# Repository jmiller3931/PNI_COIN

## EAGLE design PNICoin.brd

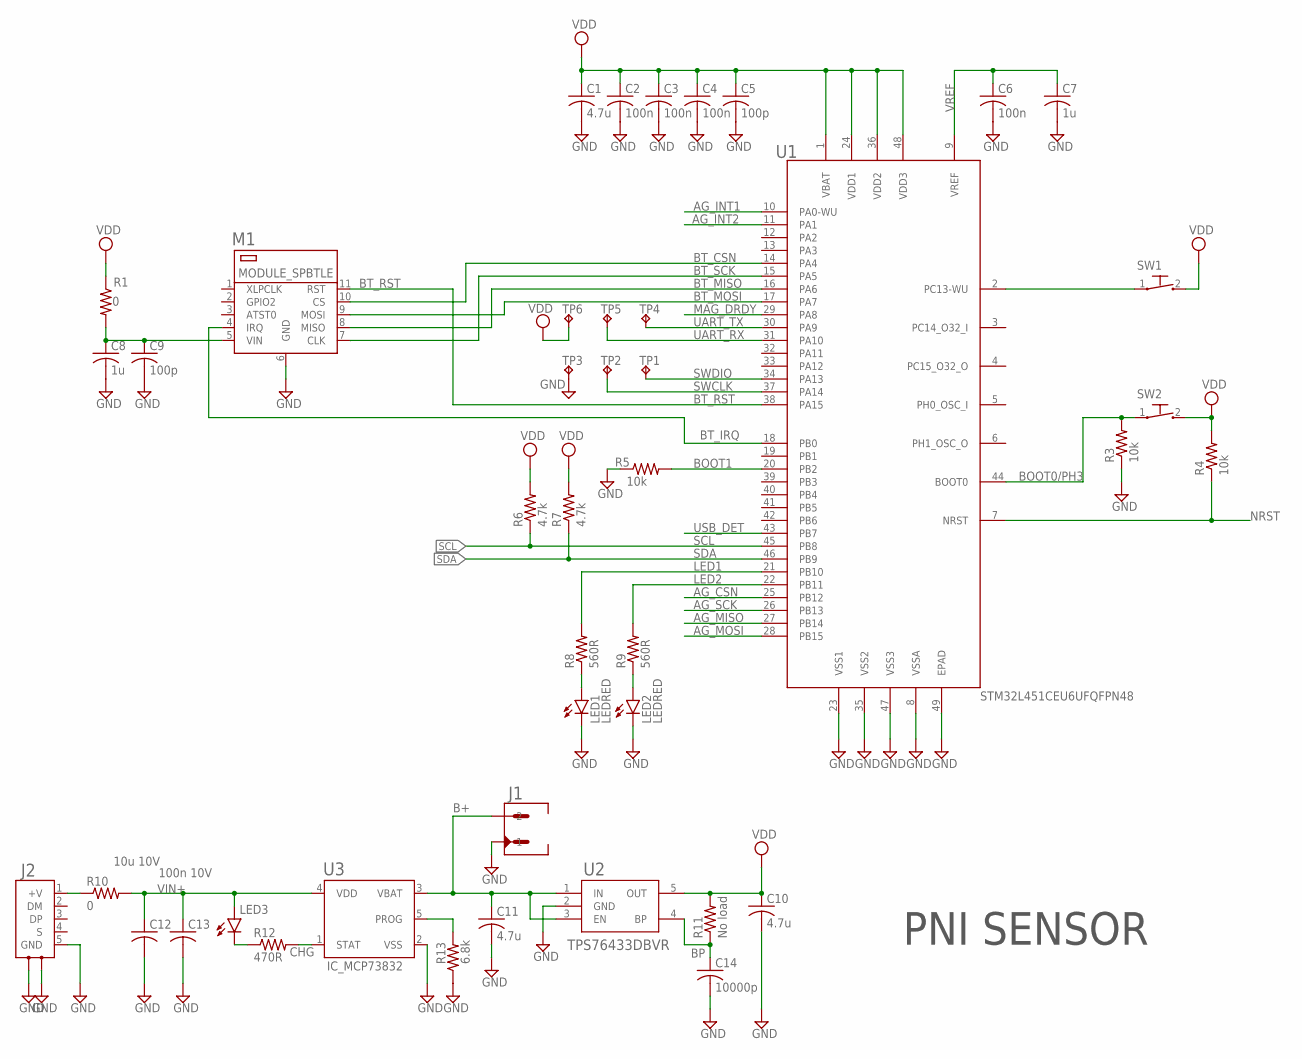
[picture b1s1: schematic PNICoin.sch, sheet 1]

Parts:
C1, C10, C11: 4.7u; C0402K
C2, C3, C4, C6: 100n; C0402K
C5, C9: 100p; C0402K
C7, C8: 1u; C0402K
C12: 10u 10V; C0402K
C13: 100n 10V; C0402K
C14: 10000p; C0402K
J1: CONN_HDR_PICO_EZMATE_2P; CON_HDR_PICO-EZMATE_2P
J2: CONN_MICROUSB_HIROSE_XZ024_SMD; CON_MICROUSB_HIROSE_XZ024_SMD
LED1, LED2, LED3: LEDRED; LED_0402
M1: MODULE_SPBTLE
R1, R10: 0; R0402
R3, R4, R5: 10k; R0402
R6, R7: 4.7k; R0402
R8, R9: 560R; R0402
R11: No load; R0402
R12: 470R; R0402
R13: 6.8k; R0402
SW1, SW2: SW_PB; SW-PB_B3U-3000PB
TP1, TP2, TP3, TP4, TP5, TP6: TPTP06R; TP06R
U1: STM32L451CEU6UFQFPN48; QFN50P700X700X60-49T560
U2: TPS76433DBVR; DBV5
U3: IC_MCP73832; SOT95P240X125-5

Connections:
AG_CSN: U1.25 (PB12); also elsewhere on the board
AG_INT1: U1.10 (PA0-WU); also elsewhere on the board
AG_INT2: U1.11 (PA1); also elsewhere on the board
AG_MISO: U1.27 (PB14); also elsewhere on the board
AG_MOSI: U1.28 (PB15); also elsewhere on the board
AG_SCK: U1.26 (PB13); also elsewhere on the board
B+: C11.1, J1.2, U2.1 (IN), U2.3 (EN), U3.3 (VBAT)
BLEV+: C8.1, C9.1, M1.5 (VIN), R1.2
BOOT0/PH3: R3.2, SW2.1, U1.44 (BOOT0)
BOOT1: R5.2, U1.20 (PB2)
BP: C14.1, R11.1, U2.4 (BP)
BT_CSN: M1.10 (CS), U1.14 (PA4)
BT_IRQ: M1.4 (IRQ), U1.18 (PB0)
BT_MISO: M1.8 (MISO), U1.16 (PA6)
BT_MOSI: M1.9 (MOSI), U1.17 (PA7)
BT_RST: M1.11 (RST), U1.38 (PA15)
BT_SCK: M1.7 (CLK), U1.15 (PA5)
CHG: R12.2, U3.1 (STAT)
GND: C1.2, C2.2, C3.2, C4.2, C5.2, C6.2, C7.2, C8.2, C9.2, C10.2, C11.2, C12.2, C13.2, C14.2, J1.1, J2.5 (GND), J2.6 (SH1), J2.7 (SH2), LED1.K (C), LED2.K (C), M1.6 (GND), R3.1, R5.1, R13.1, TP3.TP, U1.8 (VSSA), U1.23 (VSS1), U1.35 (VSS2), U1.47 (VSS3), U1.49 (EPAD), U2.2 (GND), U3.2 (VSS); also elsewhere on the board
LED1: R8.2, U1.21 (PB10)
LED1A: LED1.A, R8.1
LED2: R9.2, U1.22 (PB11)
LED2A: LED2.A, R9.1
LED3K: LED3.K (C), R12.1
MAG_DRDY: U1.29 (PA8); also elsewhere on the board
NRST: R4.1, U1.7 (NRST)
PROG: R13.2, U3.5 (PROG)
SCL: R6.1, U1.45 (PB8); also elsewhere on the board
SDA: R7.1, U1.46 (PB9); also elsewhere on the board
SW1: SW1.1, U1.2 (PC13-WU)
SWCLK: TP2.TP, U1.37 (PA14)
SWDIO: TP1.TP, U1.34 (PA13)
UART_RX: TP5.TP, U1.31 (PA10)
UART_TX: TP4.TP, U1.30 (PA9)
USB_DET: U1.43 (PB7)
VDD: C1.1, C2.1, C3.1, C4.1, C5.1, C10.1, R1.1, R4.2, R6.2, R7.2, R11.2, SW1.2, SW2.2, TP6.TP, U1.1 (VBAT), U1.24 (VDD1), U1.36 (VDD2), U1.48 (VDD3), U2.5 (OUT); also elsewhere on the board
VIN: J2.1 (+V), R10.1
VIN+: C12.1, C13.1, LED3.A, R10.2, U3.4 (VDD)
VREF: C6.1, C7.1, U1.9 (VREF)

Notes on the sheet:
PNI SENSOR

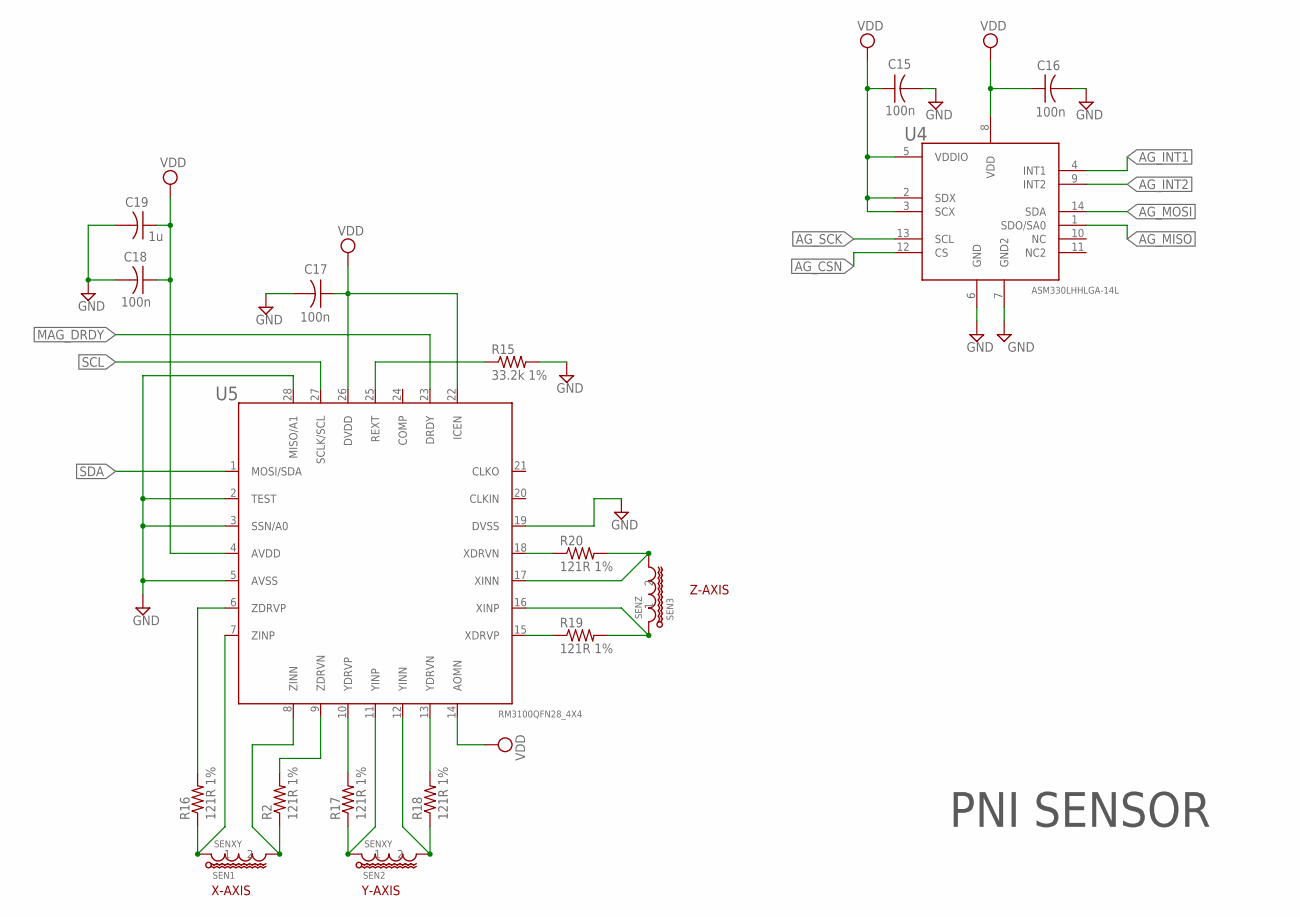
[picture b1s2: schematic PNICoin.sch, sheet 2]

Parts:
C15, C16, C17, C18: 100n; C0402K
C19: 1u; C0402K
R2, R16, R17, R18, R19, R20: 121R 1%; R0402
R15: 33.2k 1%; R0402
SEN1, SEN2: SENXY
SEN3: SENZ
U4: ASM330LHHLGA-14L; QFN50P300X250X86-14
U5: RM3100QFN28_4X4; QFN40P400X400X80-29T250

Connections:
AG_CSN: U4.12 (CS); also elsewhere on the board
AG_INT1: U4.4 (INT1); also elsewhere on the board
AG_INT2: U4.9 (INT2); also elsewhere on the board
AG_MISO: U4.1 (SDO/SA0); also elsewhere on the board
AG_MOSI: U4.14 (SDA); also elsewhere on the board
AG_SCK: U4.13 (SCL); also elsewhere on the board
GND: C15.2, C16.2, C17.2, C18.2, C19.2, R15.2, U4.6 (GND), U4.7 (GND2), U5.2 (TEST), U5.3 (SSN/A0), U5.5 (AVSS), U5.19 (DVSS), U5.28 (MISO/A1); also elsewhere on the board
MAG_DRDY: U5.23 (DRDY); also elsewhere on the board
REXT: R15.1, U5.25 (REXT)
SCL: U5.27 (SCLK/SCL); also elsewhere on the board
SDA: U5.1 (MOSI/SDA); also elsewhere on the board
VDD: C15.1, C16.1, C17.1, C18.1, C19.1, U4.2 (SDX), U4.3 (SCX), U4.5 (VDDIO), U4.8 (VDD), U5.4 (AVDD), U5.14 (AOMN), U5.22 (ICEN), U5.26 (DVDD); also elsewhere on the board
XDN: R20.1, U5.18 (XDRVN)
XDP: R19.1, U5.15 (XDRVP)
XIN: R20.2, SEN3.2, U5.17 (XINN)
XIP: R19.2, SEN3.1, U5.16 (XINP)
YDN: R18.2, U5.13 (YDRVN)
YDP: R17.2, U5.10 (YDRVP)
YIN: R18.1, SEN2.2, U5.12 (YINN)
YIP: R17.1, SEN2.1, U5.11 (YINP)
ZDN: R2.2, U5.9 (ZDRVN)
ZDP: R16.2, U5.6 (ZDRVP)
ZIN: R2.1, SEN1.2, U5.8 (ZINN)
ZIP: R16.1, SEN1.1, U5.7 (ZINP)

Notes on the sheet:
PNI SENSOR
X-AXIS
Y-AXIS
Z-AXIS

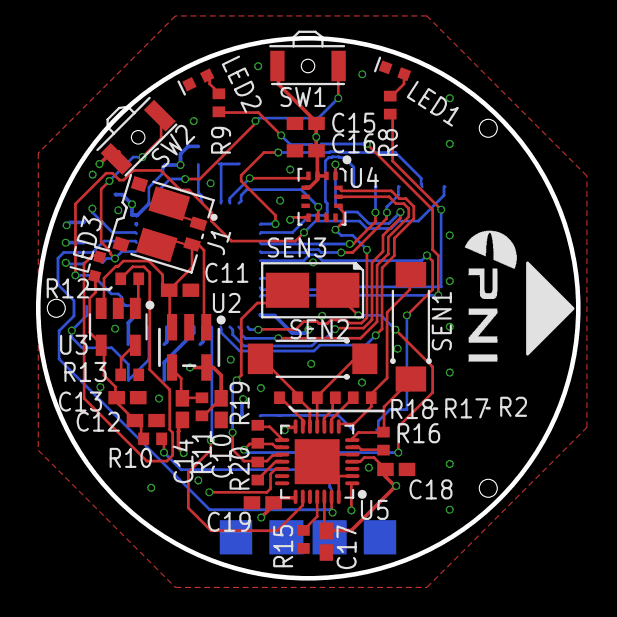
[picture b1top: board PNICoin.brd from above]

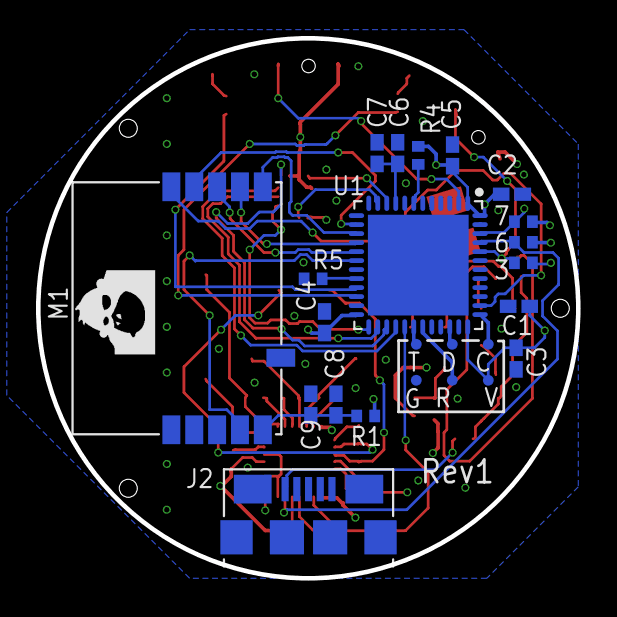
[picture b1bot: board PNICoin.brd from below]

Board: 4 copper layers, 30.0 x 30.0 mm, 62 parts (24 on the bottom side), 51 nets.

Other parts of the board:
DOC1: DOCFIELD
DOC2: LETTER_L

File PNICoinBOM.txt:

Partlist exported from C:/Users/jmiller/Documents/EAGLE/projects/PNI_COIN/PNICoin.sch at 2/7/2019 10:05 AM

Qty Value                          Device                         Package                       Parts                                   Description                MN                MP                SPICEPREFIX TP_SIGNAL_NAME
2   0                              R-US_R0402                     R0402                         R1, R10                                 RESISTOR, American symbol                                      R                         
1   10000p                         C-USC0402K                     C0402K                        C14                                     CAPACITOR, American symbol                                     C                         
9   100n                           C-USC0402K                     C0402K                        C2, C3, C4, C6, C13, C15, C16, C17, C18 CAPACITOR, American symbol                                     C                         
2   100p                           C-USC0402K                     C0402K                        C5, C9                                  CAPACITOR, American symbol                                     C                         
3   10k                            R-US_R0402                     R0402                         R3, R4, R5                              RESISTOR, American symbol                                      R                         
1   10u                            C-USC0402K                     C0402K                        C12                                     CAPACITOR, American symbol                                     C                         
6   120R 1%                        R-US_R0402                     R0402                         R2, R16, R17, R18, R19, R20             RESISTOR, American symbol                                      R                         
3   1u                             C-USC0402K                     C0402K                        C7, C8, C19                             CAPACITOR, American symbol                                     C                         
1   33.2k 1%                       R-US_R0402                     R0402                         R15                                     RESISTOR, American symbol                                      R                         
1   4.7U                           C-USC0402K                     C0402K                        C11                                     CAPACITOR, American symbol                                     C                         
1   4.7k                           C-USC0402K                     C0402K                        C10                                     CAPACITOR, American symbol                                     C                         
2   4.7k                           R-US_R0402                     R0402                         R6, R7                                  RESISTOR, American symbol                                      R                         
1   4.7u                           C-USC0402K                     C0402K                        C1                                      CAPACITOR, American symbol                                     C                         
1   470                            R-US_R0402                     R0402                         R12                                     RESISTOR, American symbol                                      R                         
2   560R                           R-US_R0402                     R0402                         R8, R9                                  RESISTOR, American symbol                                      R                         
1   6.8k                           R-US_R0402                     R0402                         R13                                     RESISTOR, American symbol                                      R                         
1   ASM330LHHLGA-14L               ASM330LHHLGA-14L               QFN50P300X250X86-14           U4                                                                 ST                ASM330LHH                                   
1   CONN_HDR_PICO_EZMATE_2P        CONN_HDR_PICO_EZMATE_2P        CON_HDR_PICO-EZMATE_2P        J1                                                                 Molex             0781710002                                  
1   CONN_MICROUSB_HIROSE_XZ024_SMD CONN_MICROUSB_HIROSE_XZ024_SMD CON_MICROUSB_HIROSE_XZ024_SMD J2                                                                 Hirose            ZX62-AB-5PA(31)                             
1   IC_MCP73832                    IC_MCP73832                    SOT95P240X125-5               U3                                                                 Microchip         MCP73832T-2ACI/OT                           
3   LEDRED                         LEDRED                         LED_0402                      LED1, LED2, LED3                        LED generic 0402           QT Brightek       QBLP595-R                                   
1   MODULE_SPBTLE                  MODULE_SPBTLE                  MODULE_SPBTLE                 M1                                                                 ST                SPBTLE-RFTR                                 
1   No load                        R-US_R0402                     R0402                         R11                                     RESISTOR, American symbol                                      R                         
1   RM3100QFN28_4X4                RM3100QFN28_4X4                QFN40P400X400X80-29T250       U5                                                                 PNI Sensor        13156                                       
2   SENXY                          SENXY                          SENXY                         SEN1, SEN2                                                         PNI Sensor        13104                                       
1   SENZ                           SENZ                           SENZ                          SEN3                                                               PNI Sensor        13101                                       
1   STM32L451CEU6UFQFPN48          STM32L451CEU6UFQFPN48          QFN50P700X700X60-49T560       U1                                                                 ST                STM32L451CEU6                               
2   SW_PB                          SW_PB                          SW-PB_B3U-3000PB              SW1, SW2                                                           Omron Electronics B3U-3000P-B                                 
1   TPS76433DBVR                   TPS76433DBVR                   DBV5                          U2                                                                 TI                TPS76433DBVR                                
6   TPTP06R                        TPTP06R                        TP06R                         TP1, TP2, TP3, TP4, TP5, TP6            Test pad

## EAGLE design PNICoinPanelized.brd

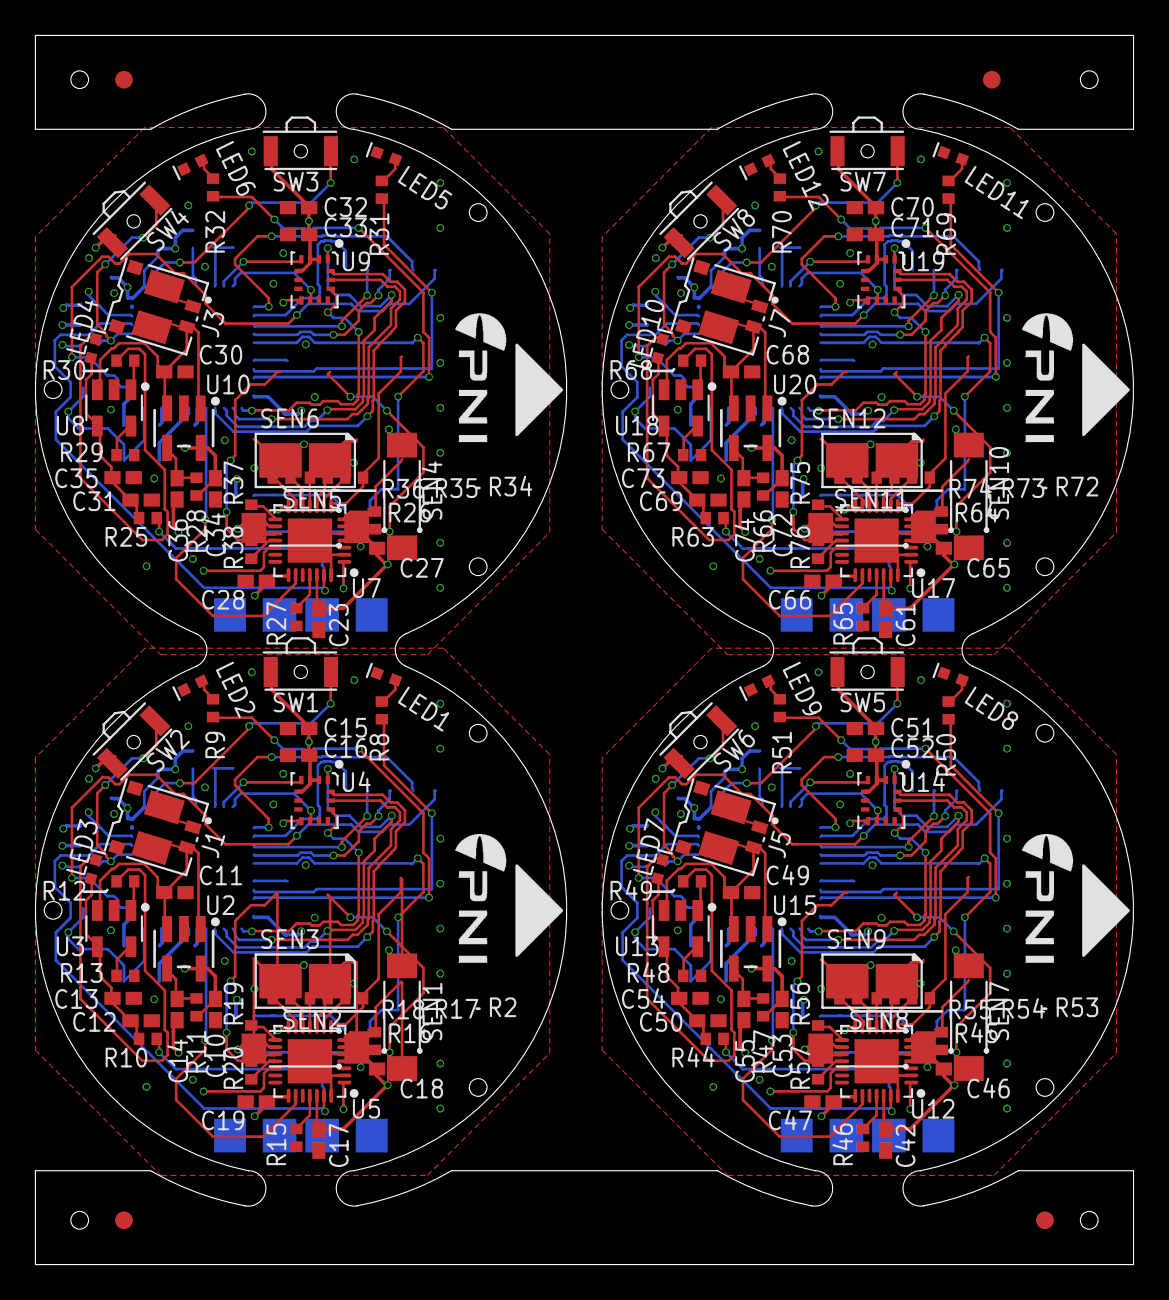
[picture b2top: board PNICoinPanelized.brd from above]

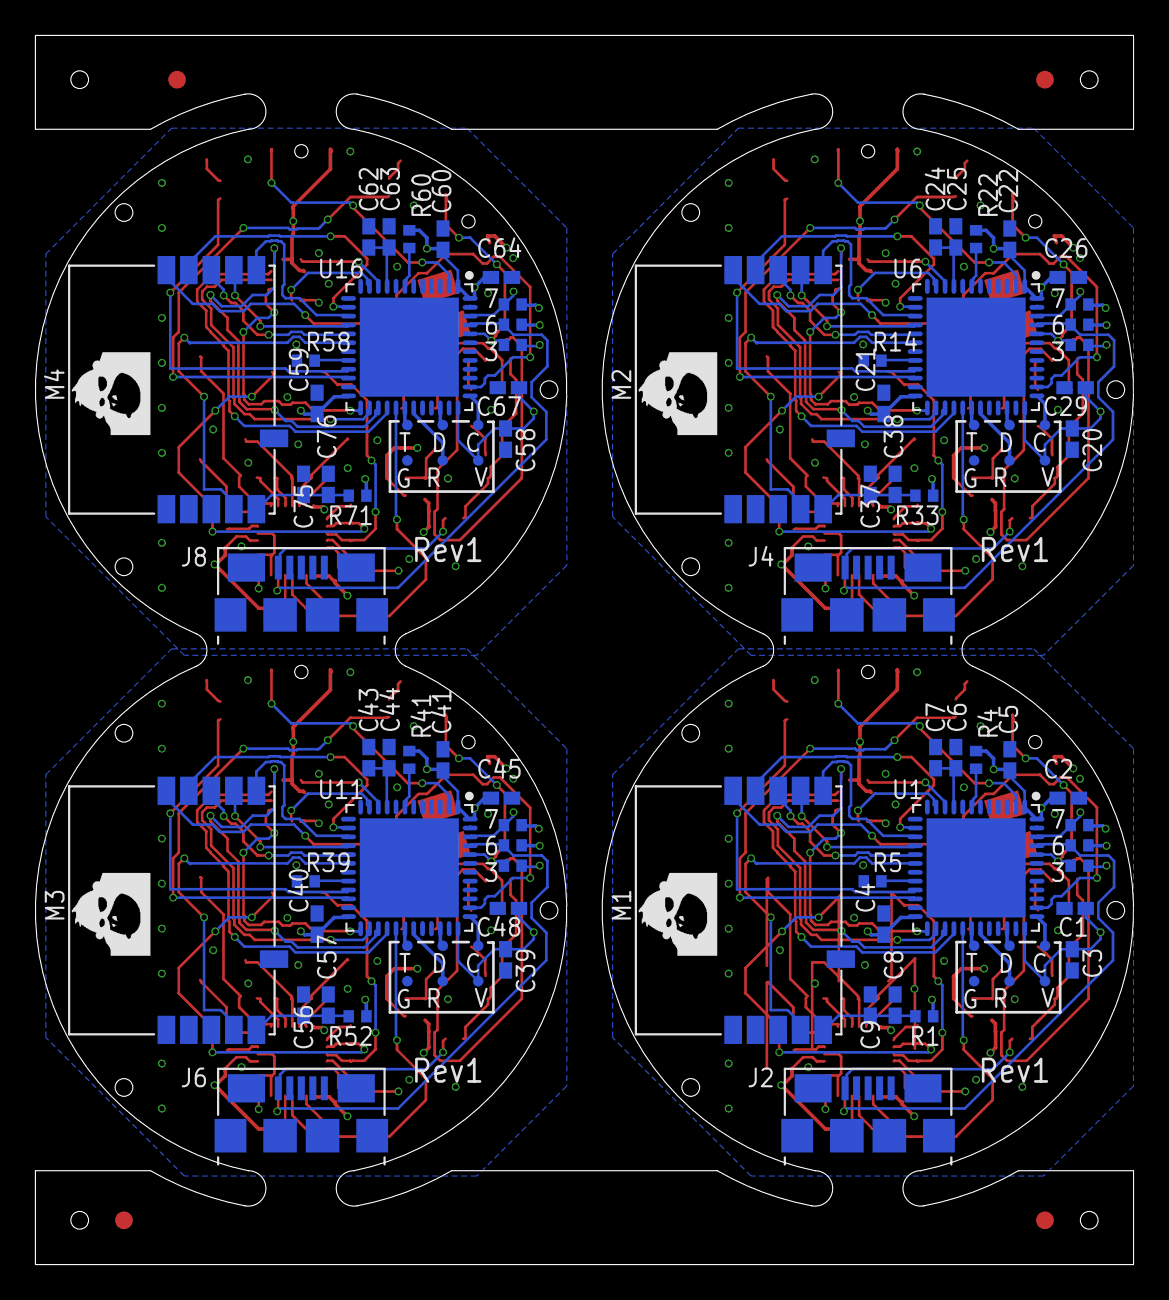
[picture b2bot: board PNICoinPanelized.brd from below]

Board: 4 copper layers, 62.0 x 69.4 mm, 242 parts (96 on the bottom side), 204 nets.

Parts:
C1, C29, C48, C67: 4.7u; C0402K
C2, C3, C4, C6, C13, C15, C16, C17, C18, C20, C21, C23, C25, C26, C27, C32, C33, C35, C39, C40, C42, C44, C45, C46, C51, C52, C54, C58, C59, C61, C63, C64, C65, C70, C71, C73: 100n; C0402K
C5, C9, C22, C37, C41, C56, C60, C75: 100p; C0402K
C7, C8, C19, C24, C28, C38, C43, C47, C57, C62, C66, C76: 1u; C0402K
C10, C34, C53, C72: 4.7k; C0402K
C11, C30, C49, C68: 4.7U; C0402K
C12, C31, C50, C69: 10u; C0402K
C14, C36, C55, C74: 10000p; C0402K
DOC1: DOCFIELD
DOC2: LETTER_L
J1, J3, J5, J7: CONN_HDR_PICO_EZMATE_2P; CON_HDR_PICO-EZMATE_2P
J2, J4, J6, J8: CONN_MICROUSB_HIROSE_XZ024_SMD; CON_MICROUSB_HIROSE_XZ024_SMD
LED1, LED2, LED3, LED4, LED5, LED6, LED7, LED8, LED9, LED10, LED11, LED12: LED; LED_0402
M1, M2, M3, M4: MODULE_SPBTLE
R1, R10, R25, R33, R44, R52, R63, R71: 0; R0402
R2, R16, R17, R18, R19, R20, R26, R34, R35, R36, R37, R38, R45, R53, R54, R55, R56, R57, R64, R72, R73, R74, R75, R76: 120R 1%; R0402
R3, R4, R5, R14, R21, R22, R39, R40, R41, R58, R59, R60: 10k; R0402
R6, R7, R23, R24, R42, R43, R61, R62: 4.7k; R0402
R8, R9, R31, R32, R50, R51, R69, R70: 560R; R0402
R11, R28, R47, R66: No load; R0402
R12, R30, R49, R68: 470; R0402
R13, R29, R48, R67: 6.8k; R0402
R15, R27, R46, R65: 33.2k 1%; R0402
SEN1, SEN2, SEN4, SEN5, SEN7, SEN8, SEN10, SEN11: SENXY
SEN3, SEN6, SEN9, SEN12: SENZ
SW1, SW2, SW3, SW4, SW5, SW6, SW7, SW8: SW_PB; SW-PB_B3U-3000PB
TP1, TP2, TP3, TP4, TP5, TP6, TP7, TP8, TP9, TP10, TP11, TP12, TP13, TP14, TP15, TP16, TP17, TP18, TP19, TP20, TP21, TP22, TP23, TP24: TPTP06R; TP06R
U1, U6, U11, U16: STM32L451CEU6UFQFPN48; QFN50P700X700X60-49T560
U2, U10, U15, U20: TPS76433DBVR; DBV5
U3, U8, U13, U18: IC_MCP73832; SOT95P240X125-5
U4, U9, U14, U19: ASM330LHHLGA-14L; QFN50P300X250X86-14
U5, U7, U12, U17: RM3100QFN28_4X4; QFN40P400X400X80-29T250

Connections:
AG_CSN: U1.25, U4.12
AG_CSN1: U6.25, U9.12
AG_CSN2: U11.25, U14.12
AG_CSN3: U16.25, U19.12
AG_INT1: U1.10, U4.4
AG_INT2: U1.11, U4.9
AG_INT3: U6.10, U9.4
AG_INT4: U6.11, U9.9
AG_INT5: U11.10, U14.4
AG_INT6: U11.11, U14.9
AG_INT7: U16.10, U19.4
AG_INT8: U16.11, U19.9
AG_MISO: U1.27, U4.1
AG_MISO1: U6.27, U9.1
AG_MISO2: U11.27, U14.1
AG_MISO3: U16.27, U19.1
AG_MOSI: U1.28, U4.14
AG_MOSI1: U6.28, U9.14
AG_MOSI2: U11.28, U14.14
AG_MOSI3: U16.28, U19.14
AG_SCK: U1.26, U4.13
AG_SCK1: U6.26, U9.13
AG_SCK2: U11.26, U14.13
AG_SCK3: U16.26, U19.13
B+: C11.1, J1.2, U2.1, U2.3, U3.3
B+1: C30.1, J3.2, U8.3, U10.1, U10.3
B+2: C49.1, J5.2, U13.3, U15.1, U15.3
B+3: C68.1, J7.2, U18.3, U20.1, U20.3
BLEV+: C8.1, C9.1, M1.5, R1.2
BLEV+1: C37.1, C38.1, M2.5, R33.2
BLEV+2: C56.1, C57.1, M3.5, R52.2
BLEV+3: C75.1, C76.1, M4.5, R71.2
BOOT0/PH1: R21.2, SW4.1, U6.44
BOOT0/PH2: R40.2, SW6.1, U11.44
BOOT0/PH3: R3.2, SW2.1, U1.44
BOOT0/PH4: R59.2, SW8.1, U16.44
BOOT1: R5.2, U1.20
BOOT2: R14.2, U6.20
BOOT3: R39.2, U11.20
BOOT4: R58.2, U16.20
BP: C14.1, R11.1, U2.4
BP1: C36.1, R28.1, U10.4
BP2: C55.1, R47.1, U15.4
BP3: C74.1, R66.1, U20.4
BT_CSN: M1.10, U1.14
BT_CSN1: M2.10, U6.14
BT_CSN2: M3.10, U11.14
BT_CSN3: M4.10, U16.14
BT_IRQ: M1.4, U1.18
BT_IRQ1: M2.4, U6.18
BT_IRQ2: M3.4, U11.18
BT_IRQ3: M4.4, U16.18
BT_MISO: M1.8, U1.16
BT_MISO1: M2.8, U6.16
BT_MISO2: M3.8, U11.16
BT_MISO3: M4.8, U16.16
BT_MOSI: M1.9, U1.17
BT_MOSI1: M2.9, U6.17
BT_MOSI2: M3.9, U11.17
BT_MOSI3: M4.9, U16.17
BT_RST: M1.11, U1.38
BT_RST1: M2.11, U6.38
BT_RST2: M3.11, U11.38
BT_RST3: M4.11, U16.38
BT_SCK: M1.7, U1.15
BT_SCK1: M2.7, U6.15
BT_SCK2: M3.7, U11.15
BT_SCK3: M4.7, U16.15
CHG: R12.2, U3.1
CHG1: R30.2, U8.1
CHG2: R49.2, U13.1
CHG3: R68.2, U18.1
GND: C1.2, C2.2, C3.2, C4.2, C5.2, C6.2, C7.2, C8.2, C9.2, C10.2, C11.2, C12.2, C13.2, C14.2, C15.2, C16.2, C17.2, C18.2, C19.2, J1.1, J2.5, J2.6, J2.7, LED1.K, LED2.K, M1.6, R3.1, R5.1, R13.1, R15.2, TP3.TP, U1.8, U1.23, U1.35, U1.47, U1.49, U2.2, U3.2, U4.6, U4.7, U5.2, U5.3, U5.5, U5.19, U5.28
GND1: C20.2, C21.2, C22.2, C23.2, C24.2, C25.2, C26.2, C27.2, C28.2, C29.2, C30.2, C31.2, C32.2, C33.2, C34.2, C35.2, C36.2, C37.2, C38.2, J3.1, J4.5, J4.6, J4.7, LED5.K, LED6.K, M2.6, R14.1, R21.1, R27.2, R29.1, TP9.TP, U6.8, U6.23, U6.35, U6.47, U6.49, U7.2, U7.3, U7.5, U7.19, U7.28, U8.2, U9.6, U9.7, U10.2
GND2: C39.2, C40.2, C41.2, C42.2, C43.2, C44.2, C45.2, C46.2, C47.2, C48.2, C49.2, C50.2, C51.2, C52.2, C53.2, C54.2, C55.2, C56.2, C57.2, J5.1, J6.5, J6.6, J6.7, LED8.K, LED9.K, M3.6, R39.1, R40.1, R46.2, R48.1, TP15.TP, U11.8, U11.23, U11.35, U11.47, U11.49, U12.2, U12.3, U12.5, U12.19, U12.28, U13.2, U14.6, U14.7, U15.2
GND3: C58.2, C59.2, C60.2, C61.2, C62.2, C63.2, C64.2, C65.2, C66.2, C67.2, C68.2, C69.2, C70.2, C71.2, C72.2, C73.2, C74.2, C75.2, C76.2, J7.1, J8.5, J8.6, J8.7, LED11.K, LED12.K, M4.6, R58.1, R59.1, R65.2, R67.1, TP21.TP, U16.8, U16.23, U16.35, U16.47, U16.49, U17.2, U17.3, U17.5, U17.19, U17.28, U18.2, U19.6, U19.7, U20.2
LED1: R8.2, U1.21
LED1A: LED1.A, R8.1
LED1A1: LED5.A, R31.1
LED1A2: LED8.A, R50.1
LED1A3: LED11.A, R69.1
LED2: R9.2, U1.22
LED2A: LED2.A, R9.1
LED2A1: LED6.A, R32.1
LED2A2: LED9.A, R51.1
LED2A3: LED12.A, R70.1
LED3: R31.2, U6.21
LED3K: LED3.K, R12.1
LED3K1: LED4.K, R30.1
LED3K2: LED7.K, R49.1
LED3K3: LED10.K, R68.1
LED4: R32.2, U6.22
LED5: R50.2, U11.21
LED6: R51.2, U11.22
LED7: R69.2, U16.21
LED8: R70.2, U16.22
MAG_DRDY: U1.29, U5.23
MAG_DRDY1: U6.29, U7.23
MAG_DRDY2: U11.29, U12.23
MAG_DRDY3: U16.29, U17.23
NRST: R4.1, U1.7
NRST1: R22.1, U6.7
NRST2: R41.1, U11.7
NRST3: R60.1, U16.7
PROG: R13.2, U3.5
PROG1: R29.2, U8.5
PROG2: R48.2, U13.5
PROG3: R67.2, U18.5
REXT: R15.1, U5.25
REXT1: R27.1, U7.25
REXT2: R46.1, U12.25
REXT3: R65.1, U17.25
SCL: R6.1, U1.45, U5.27
SCL1: R23.1, U6.45, U7.27
SCL2: R42.1, U11.45, U12.27
SCL3: R61.1, U16.45, U17.27
SDA: R7.1, U1.46, U5.1
SDA1: R24.1, U6.46, U7.1
SDA2: R43.1, U11.46, U12.1
SDA3: R62.1, U16.46, U17.1
SW1: SW1.1, U1.2
SW2: SW3.1, U6.2
SW3: SW5.1, U11.2
SW4: SW7.1, U16.2
SWCLK: TP2.TP, U1.37
SWCLK1: TP8.TP, U6.37
SWCLK2: TP14.TP, U11.37
SWCLK3: TP20.TP, U16.37
SWDIO: TP1.TP, U1.34
SWDIO1: TP7.TP, U6.34
SWDIO2: TP13.TP, U11.34
SWDIO3: TP19.TP, U16.34
UART_RX: TP5.TP, U1.31
UART_RX1: TP11.TP, U6.31
UART_RX2: TP17.TP, U11.31
UART_RX3: TP23.TP, U16.31
UART_TX: TP4.TP, U1.30
UART_TX1: TP10.TP, U6.30
UART_TX2: TP16.TP, U11.30
UART_TX3: TP22.TP, U16.30
VDD: C1.1, C2.1, C3.1, C4.1, C5.1, C10.1, C15.1, C16.1, C17.1, C18.1, C19.1, R1.1, R4.2, R6.2, R7.2, R11.2, SW1.2, SW2.2, TP6.TP, U1.1, U1.24, U1.36, U1.48, U2.5, U4.2, U4.3, U4.5, U4.8, U5.4, U5.14, U5.22, U5.26
VDD1: C20.1, C21.1, C22.1, C23.1, C26.1, C27.1, C28.1, C29.1, C32.1, C33.1, C34.1, R22.2, R23.2, R24.2, R28.2, R33.1, SW3.2, SW4.2, TP12.TP, U6.1, U6.24, U6.36, U6.48, U7.4, U7.14, U7.22, U7.26, U9.2, U9.3, U9.5, U9.8, U10.5
VDD2: C39.1, C40.1, C41.1, C42.1, C45.1, C46.1, C47.1, C48.1, C51.1, C52.1, C53.1, R41.2, R42.2, R43.2, R47.2, R52.1, SW5.2, SW6.2, TP18.TP, U11.1, U11.24, U11.36, U11.48, U12.4, U12.14, U12.22, U12.26, U14.2, U14.3, U14.5, U14.8, U15.5
VDD3: C58.1, C59.1, C60.1, C61.1, C64.1, C65.1, C66.1, C67.1, C70.1, C71.1, C72.1, R60.2, R61.2, R62.2, R66.2, R71.1, SW7.2, SW8.2, TP24.TP, U16.1, U16.24, U16.36, U16.48, U17.4, U17.14, U17.22, U17.26, U19.2, U19.3, U19.5, U19.8, U20.5
VIN: J2.1, R10.1
VIN1: J4.1, R25.1
VIN2: J6.1, R44.1
VIN3: J8.1, R63.1
VIN+: C12.1, C13.1, LED3.A, R10.2, U3.4
VIN+1: C31.1, C35.1, LED4.A, R25.2, U8.4
VIN+2: C50.1, C54.1, LED7.A, R44.2, U13.4
VIN+3: C69.1, C73.1, LED10.A, R63.2, U18.4
VREF: C6.1, C7.1, U1.9
VREF1: C24.1, C25.1, U6.9
VREF2: C43.1, C44.1, U11.9
VREF3: C62.1, C63.1, U16.9
XDN: R20.1, U5.18
XDN1: R38.1, U7.18
XDN2: R57.1, U12.18
XDN3: R76.1, U17.18
XDP: R19.1, U5.15
XDP1: R37.1, U7.15
XDP2: R56.1, U12.15
XDP3: R75.1, U17.15
XIN: R20.2, SEN3.2, U5.17
XIN1: R38.2, SEN6.2, U7.17
XIN2: R57.2, SEN9.2, U12.17
XIN3: R76.2, SEN12.2, U17.17
XIP: R19.2, SEN3.1, U5.16
XIP1: R37.2, SEN6.1, U7.16
XIP2: R56.2, SEN9.1, U12.16
XIP3: R75.2, SEN12.1, U17.16
YDN: R18.2, U5.13
YDN1: R36.2, U7.13
YDN2: R55.2, U12.13
YDN3: R74.2, U17.13
YDP: R17.2, U5.10
YDP1: R35.2, U7.10
YDP2: R54.2, U12.10
YDP3: R73.2, U17.10
YIN: R18.1, SEN2.2, U5.12
YIN1: R36.1, SEN5.2, U7.12
YIN2: R55.1, SEN8.2, U12.12
YIN3: R74.1, SEN11.2, U17.12
YIP: R17.1, SEN2.1, U5.11
YIP1: R35.1, SEN5.1, U7.11
YIP2: R54.1, SEN8.1, U12.11
YIP3: R73.1, SEN11.1, U17.11
ZDN: R2.2, U5.9
ZDN1: R34.2, U7.9
ZDN2: R53.2, U12.9
ZDN3: R72.2, U17.9
ZDP: R16.2, U5.6
ZDP1: R26.2, U7.6
ZDP2: R45.2, U12.6
ZDP3: R64.2, U17.6
ZIN: R2.1, SEN1.2, U5.8
ZIN1: R34.1, SEN4.2, U7.8
ZIN2: R53.1, SEN7.2, U12.8
ZIN3: R72.1, SEN10.2, U17.8
ZIP: R16.1, SEN1.1, U5.7
ZIP1: R26.1, SEN4.1, U7.7
ZIP2: R45.1, SEN7.1, U12.7
ZIP3: R64.1, SEN10.1, U17.7
